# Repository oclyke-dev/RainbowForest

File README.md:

# Rainbow Forest

Rainbow Forest is an interactive experience to compose short songs on a larger-than-life musical staff. Designed for the Museum of Boulder's 2020 Plazeum 2.0 exhibit this installation engages creativity and interaction through the combination of sounds and sights.

## Firmware

There are several microcontrollers working in concert (pun intended) to make the Rainbow Forest function. They are:

- **conductor** : the main processor conducting audio operations and the overall system operation
- **network hub** : the network hub handles communication between the column controllers and the conductor 
- **column controllers** : each column of notes on the staff is managed by an individual controller

The programs that run on each of these devices can be found in ```firmware/main```

Components that are common between programs can be found in ```firmware/components```. These components are expected to be symbolically linked into the main program directories. Arduino requires additional source code to be placed within a ```src``` directory. From the repository root directory one may run the link scripts to quickly make symbolic links from every component to every main program. 

- **linux**: ```./scripts/link.sh```
- **windows**: ```scripts\link.bat```

You may also create the symbolic links manually (Linux / Windows examples follow).

- **linux**: ```ln -s firmware/components/${component} firmware/main/${program}/src/components```
- **windows**: ```mklink /J firmware\main\%program%\src\components\%component% firmware\components\%component%```

Partial / experimental programs may be contained in ```firmware/prototyping``` for reference

## Hardware

The hardware directory contains the Eagle design files and Gerber manufacturing files for the original Rainbow Forest installation.

## Web

The Rainbow Forest installation connects to the world wide web, allowing users to check in on its status from anywhere.

In the museum a single-board computer running Chromium is used as a dedicated user interface.

```
./Chromium.app/Contents/MacOS/Chromium --app=https://oclyke.dev/rainbow-forest
```

## raspberry pi
the rainbow forest uses a local raspberry pi microcomputer to provide a user interface for museum visitors. this is acheived by using Chromium in kiosk mode. the raspberry pi also translates ```ws://``` messages into ```wss://``` messages for transfer to the main server (since the esp32s were unhappy running ```wss://```) 

[headless raspberry pi configuration](https://desertbot.io/blog/headless-raspberry-pi-3-bplus-ssh-wifi-setup)
[configuring rapberry pi for kiosk mode](https://die-antwort.eu/techblog/2017-12-setup-raspberry-pi-for-kiosk-mode/)
[using systemd on the pi](https://www.raspberrypi.org/documentation/linux/usage/systemd.md)
[using node and pm2 to daemonize applications](https://dev.to/bogdaaamn/run-your-nodejs-application-on-a-headless-raspberry-pi-4jnn)
[distributions of node for raspberry pi](https://github.com/nodesource/distributions)

## License

This project is subject to the license listed in file ```LICENSE.md```

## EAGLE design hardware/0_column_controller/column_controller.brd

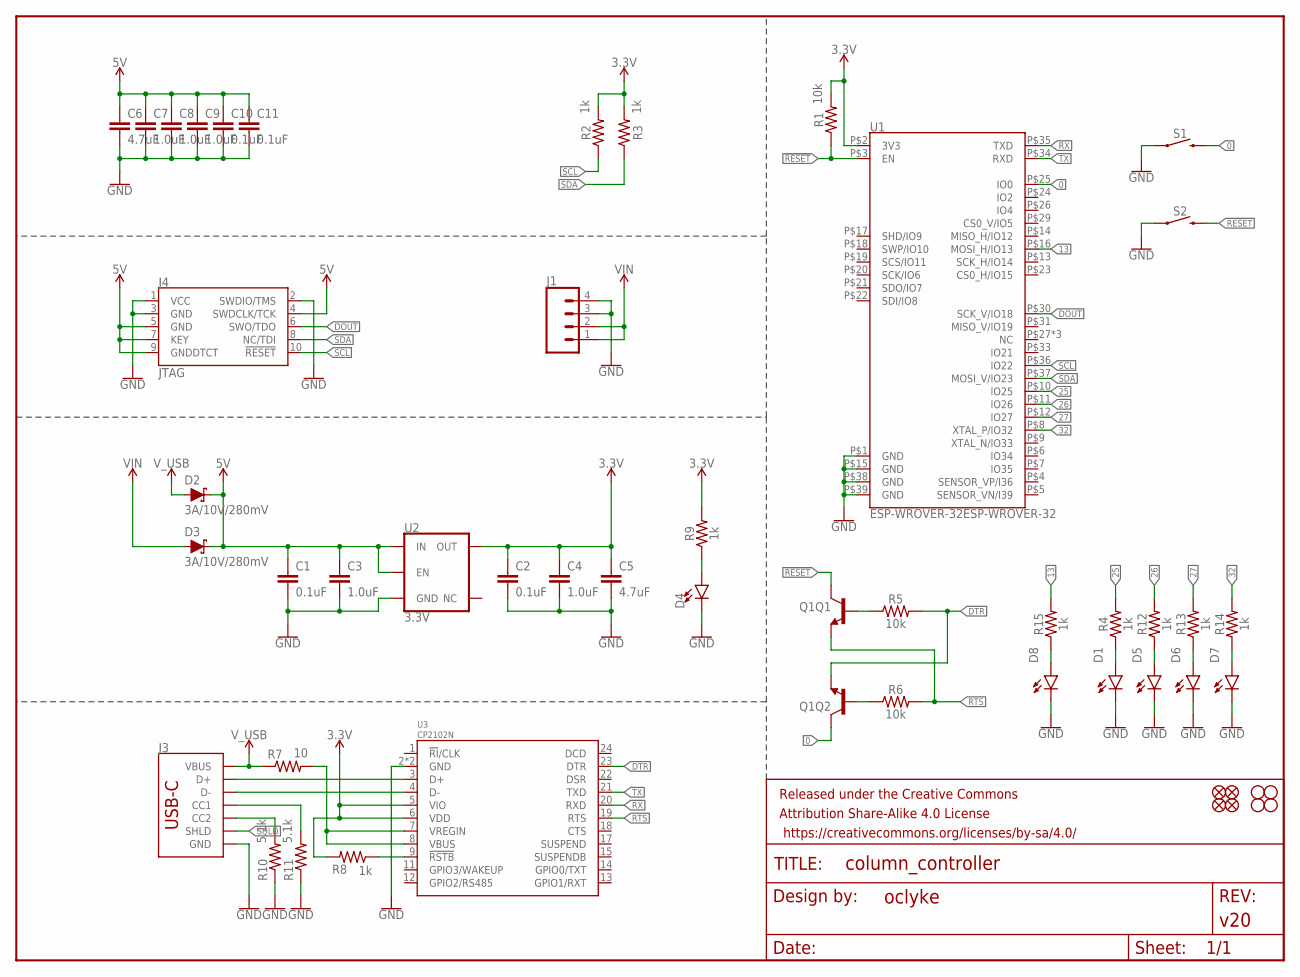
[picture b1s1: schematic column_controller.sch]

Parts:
C1, C2, C10, C11: 0.1uF; 0603
C3, C4, C7, C8, C9: 1.0uF; 0603
C5, C6: 4.7uF; 0603
D1, D5, D6, D7, D8: LED-BLUE0603; LED-0603
D2, D3: 3A/10V/280mV; SOD-323
D4: LED-RED0603; LED-0603
FD1, FD2, FD3, FD4: FIDUCIAL1X2; FIDUCIAL-1X2
FRAME1: FRAME-LETTER; CREATIVE_COMMONS
H1, H2, H3, H4: STAND-OFF#8; STAND-OFF-#8
J1: CONN_04SCREW; SCREWTERMINAL-3.5MM-4
J3: USB_C_2-LAYER; USB-C-16P
J4: JTAG; 2X5-SMD-1.27MM
Q1: TRANS_NPN_DUAL-MBT3904DW1T1; SC70-6
R1, R5, R6: 10k; 0603
R2, R3, R4, R8, R9, R12, R13, R14, R15: 1k; 0603
R7: 10; 0603
R10, R11: 5.1k; 0603
S1, S2: MOMENTARY-SWITCH-SPST-SMD-4.6X2.8MM; TACTILE_SWITCH_SMD_4.6X2.8MM
U1: ESP-WROVER-32ESP-WROVER-32; ESP-WROVER-32
U2: 3.3V; SOT23-5
U3: CP2102N; QFN24

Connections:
0: Q1.6 (C), S1.3 (2), S1.4 (2), U1.P$25 (IO0)
3.3V: C2.1, C4.1, C5.1, R1.2, R2.2, R3.2, R8.2, R9.2, U1.P$2 (3V3), U2.5 (OUT), U3.5 (VIO), U3.6 (VDD)
5V: C1.1, C3.1, C6.1, C7.1, C8.1, C9.1, C10.1, C11.1, D2.C, D3.C, J4.4 (SWDCLK/TCK), J4.5 (GND), J4.7 (KEY), J4.9 (GNDDTCT), U2.1 (IN), U2.3 (EN)
13: R15.2, U1.P$16 (MOSI_H/IO13)
25: R4.2, U1.P$10 (IO25)
26: R12.2, U1.P$11 (IO26)
27: R13.2, U1.P$12 (IO27)
32: R14.2, U1.P$8 (XTAL_P/IO32)
!RESET: Q1.3 (C), R1.1, S2.3 (2), S2.4 (2), U1.P$3 (EN)
DOUT: J4.6 (SWO/TDO), U1.P$30 (SCK_V/IO18)
DTR: Q1.1 (E), R5.2, U3.23 (DTR)
GND: C1.2, C2.2, C3.2, C4.2, C5.2, C6.2, C7.2, C8.2, C9.2, C10.2, C11.2, D1.C, D4.C, D5.C, D6.C, D7.C, D8.C, J1.3, J1.4, J3.GND, J3.GND2 (GND), J4.1 (VCC), J4.2 (SWDIO/TMS), J4.3 (GND), R10.1, R11.1, S1.1, S1.2 (1), S2.1, S2.2 (1), U1.P$1 (GND), U1.P$15 (GND), U1.P$38 (GND), U1.P$39 (GND), U2.2 (GND), U3.2 (GND), U3.PAD (GND)
unnamed: J3.A7 (D-), J3.B7 (D-), U3.4 (D-)
unnamed: J3.A6 (D+), J3.B6 (D+), U3.3 (D+)
unnamed: Q1.2 (B), R6.1
unnamed: D1.A, R4.1
unnamed: Q1.5 (B), R5.1
unnamed: R7.2, U3.7 (VREGIN), U3.8 (VBUS)
unnamed: R8.1, U3.9 (!RSTB)
unnamed: D4.A, R9.1
unnamed: D5.A, R12.1
unnamed: J3.A5 (CC1), R11.2
unnamed: J3.B5 (CC2), R10.2
unnamed: D6.A, R13.1
unnamed: D7.A, R14.1
unnamed: D8.A, R15.1
RTS: Q1.4 (E), R6.2, U3.19 (RTS)
RX: U1.P$35 (TXD), U3.20 (RXD)
SCL: J4.10 (!RESET), R2.1, U1.P$36 (IO22)
SDA: J4.8 (NC/TDI), R3.1, U1.P$37 (MOSI_V/IO23)
SHLD: J3.SHLD1 (SHLD), J3.SHLD2 (SHLD), J3.SHLD3 (SHLD), J3.SHLD4 (SHLD), J3.SHLD5 (SHLD), J3.SHLD6 (SHLD), J3.SHLD7 (SHLD), J3.SHLD8 (SHLD)
TX: U1.P$34 (RXD), U3.21 (TXD)
VIN: D3.A, J1.1, J1.2
V_USB: D2.A, J3.VBUS1 (VBUS), J3.VBUS2 (VBUS), R7.1

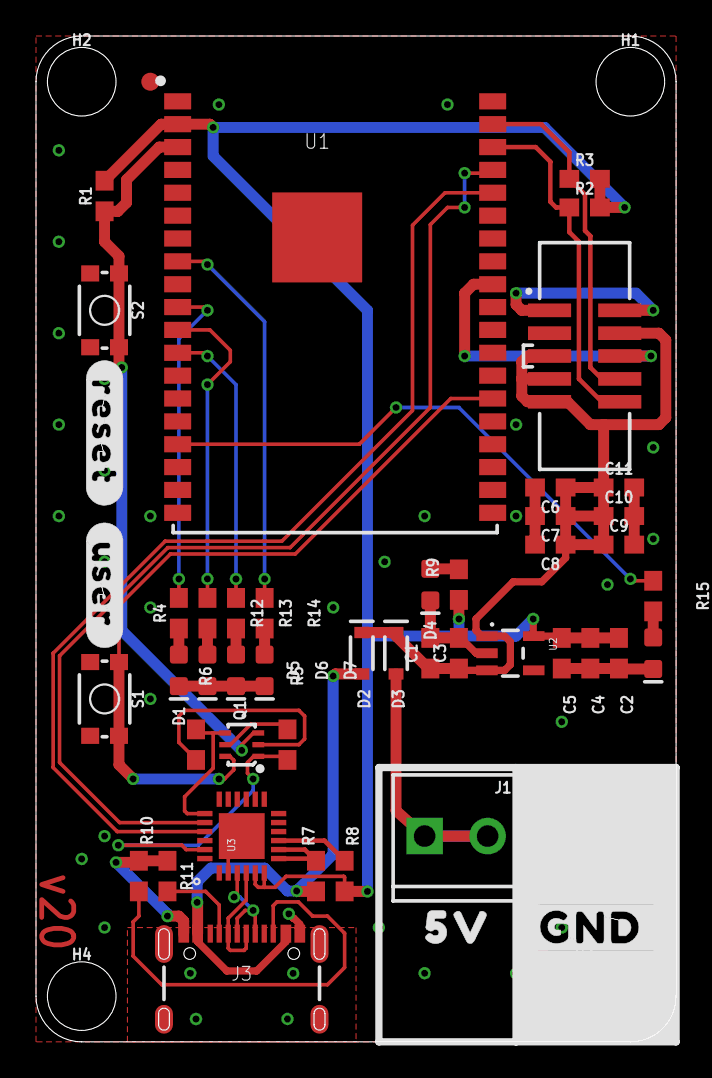
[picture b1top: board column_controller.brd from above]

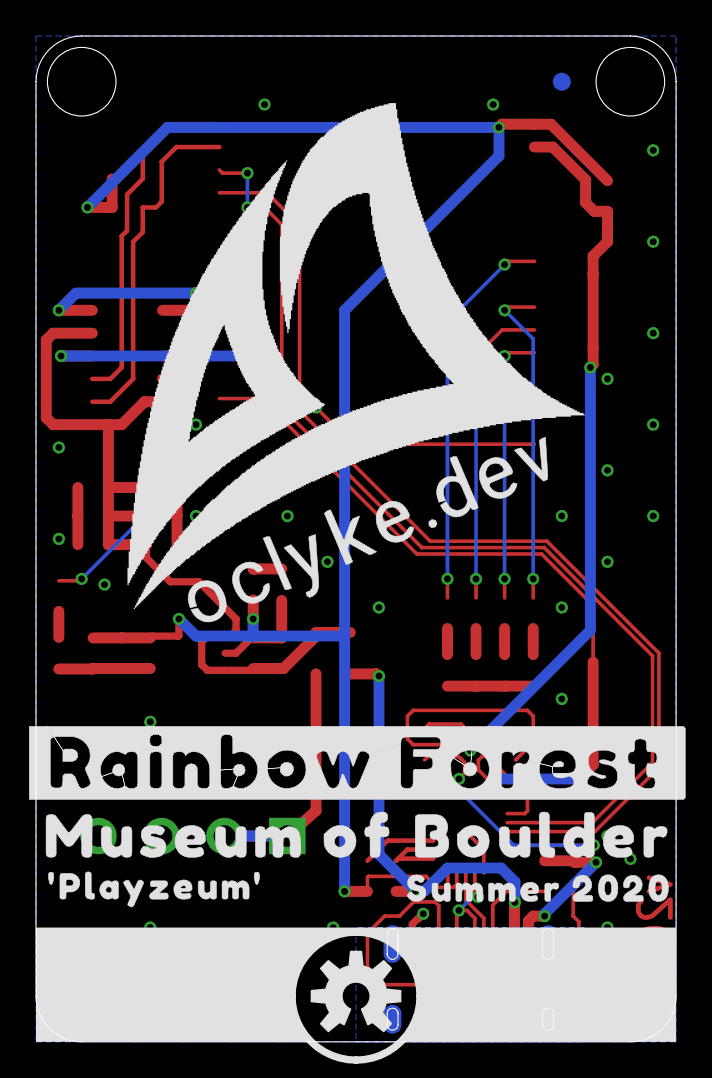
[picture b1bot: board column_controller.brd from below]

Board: 2 copper layers, 35.5 x 55.9 mm, 63 parts (9 on the bottom side), 34 nets.

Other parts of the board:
U$1: 5V2
U$2: #GND#6
U$4: #USER#2
U$5: #RESET#3
U$6: OCL_L#PNG
U$7: MUSEUM_OF_BOULDER9
U$8: OCLYKE#DEV7
U$9: #RAINBOW_FOREST#8
U$10: SUMMER_202010
U$11: #PLAYZEUM#10
U$12: OSHW-LOGO-M

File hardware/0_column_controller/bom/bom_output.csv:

Qty, PROD_ID, Names, Value, Package
4, CAP-00810, C1; C2; C10; C11, 0.1uF, 0603
5, CAP-13930, C3; C4; C7; C8; C9, 1.0uF, 0603
2, CAP-14106, C5; C6, 4.7uF, 0603
5, DIO-08575, D1; D5; D6; D7; D8, , LED-0603
2, DIO-14072, D2; D3, 3A/10V/280mV, SOD-323
1, DIO-00819, D4, , LED-0603
1, CONN-14485, J1, , SCREWTERMINAL-3.5MM-4
1, CONN-14122, J3, , USB-C-16P
1, CONN-14503, J4, JTAG, 2X5-SMD-1.27MM
1, TRANS-13337, Q1, , SC70-6
3, RES-00824, R1; R5; R6, 10k, 0603
9, RES-07856, R2; R3; R4; R8; R9; R12; R13; R14; R15, 1k, 0603
1, RES-12581, R7, 10, 0603
2, RES-12083, R10; R11, 5.1k, 0603
2, SWCH-13065, S1; S2, , TACTILE_SWITCH_SMD_4.6X2.8MM
1, , U1, ESP-WROVER-32ESP-WROVER-32, ESP-WROVER-32
1, VREG-12457, U2, 3.3V, SOT23-5
1, IC-14020, U3, CP2102N, QFN24

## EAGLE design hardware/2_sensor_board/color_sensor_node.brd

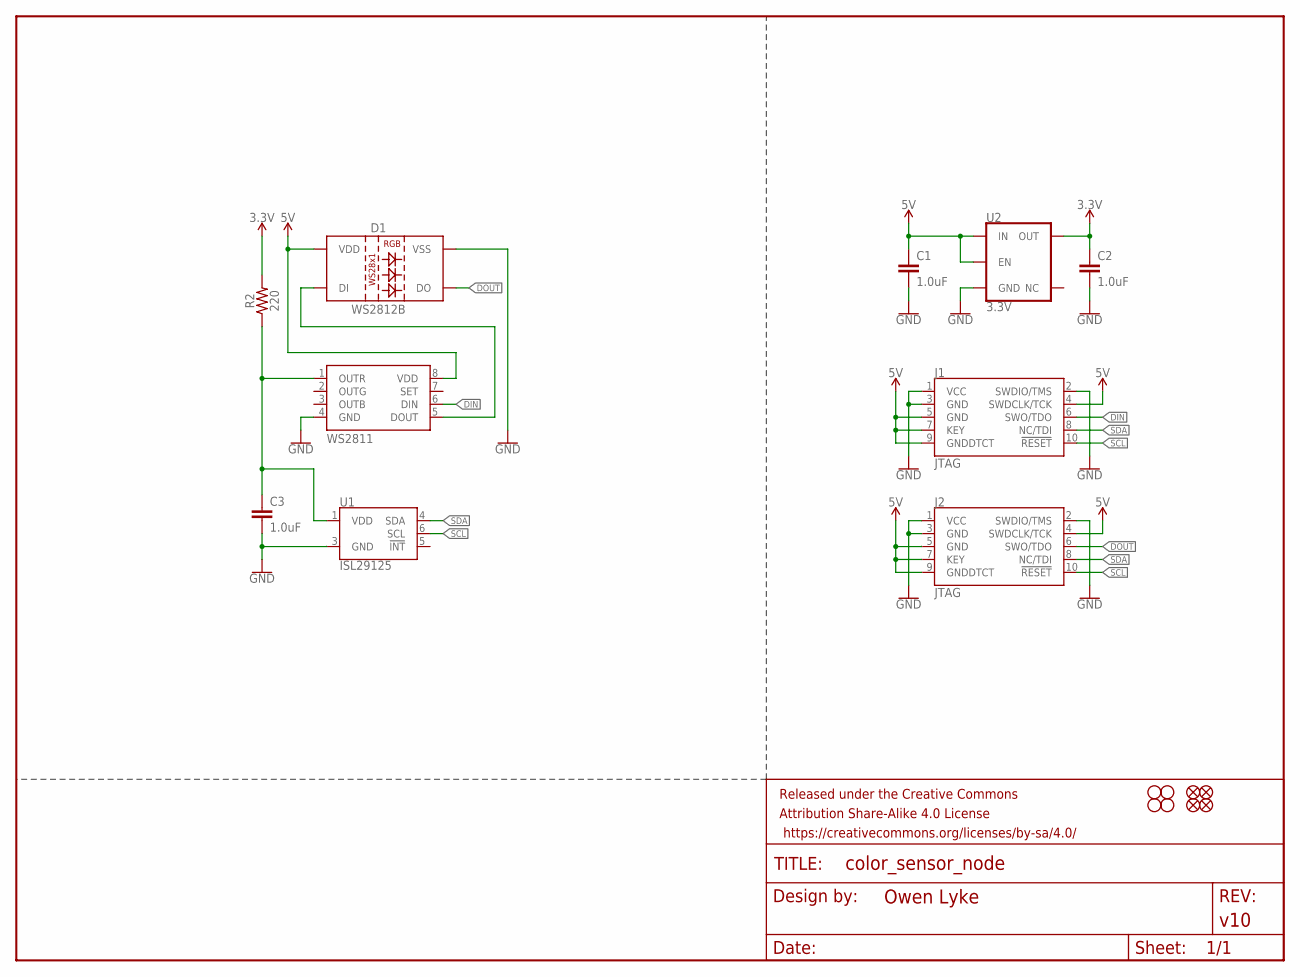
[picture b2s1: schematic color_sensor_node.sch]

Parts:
C1, C2, C3: 1.0uF; 0603
D1: WS2812B; WS2812-2020
FD1, FD2, FD3, FD4: FIDUCIAL1X2; FIDUCIAL-1X2
FRAME1: FRAME-LETTER; CREATIVE_COMMONS
H1, H2, H3, H4: STAND-OFF#8; STAND-OFF-#8
J1, J2: JTAG; 2X5-SMD-1.27MM
R2: 220; 0603
U1: ISL29125; ODFN-6
U2: 3.3V; SOT23-5
U3: WS2811; SOIC-8

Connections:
3.3V: C2.1, R2.2, U2.5 (OUT)
5V: C1.1, D1.4 (VDD), J1.4 (SWDCLK/TCK), J1.5 (GND), J1.7 (KEY), J1.9 (GNDDTCT), J2.4 (SWDCLK/TCK), J2.5 (GND), J2.7 (KEY), J2.9 (GNDDTCT), U2.1 (IN), U2.3 (EN), U3.8 (VDD)
DIN: J1.6 (SWO/TDO), U3.6 (DIN)
DOUT: D1.1 (DO), J2.6 (SWO/TDO)
GND: C1.2, C2.2, C3.2, D1.2 (VSS), J1.1 (VCC), J1.2 (SWDIO/TMS), J1.3 (GND), J2.1 (VCC), J2.2 (SWDIO/TMS), J2.3 (GND), U1.3 (GND), U2.2 (GND), U3.4 (GND)
unnamed: C3.1, R2.1, U1.1 (VDD), U3.1 (OUTR)
unnamed: D1.3 (DI), U3.5 (DOUT)
SCL: J1.10 (!RESET), J2.10 (!RESET), U1.6 (SCL)
SDA: J1.8 (NC/TDI), J2.8 (NC/TDI), U1.4 (SDA)

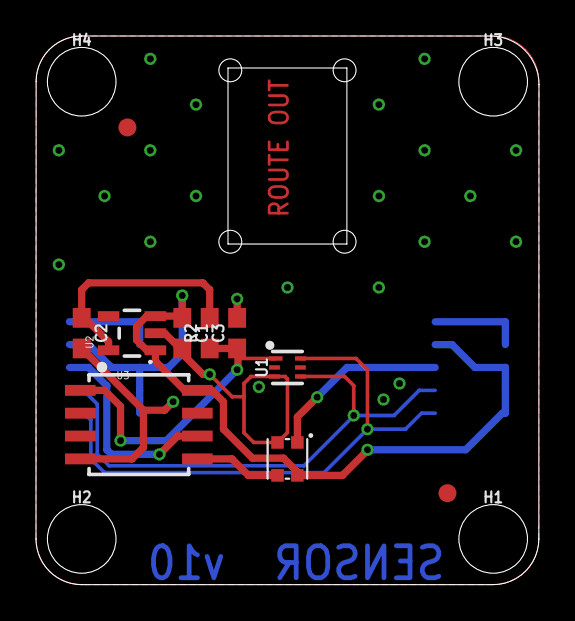
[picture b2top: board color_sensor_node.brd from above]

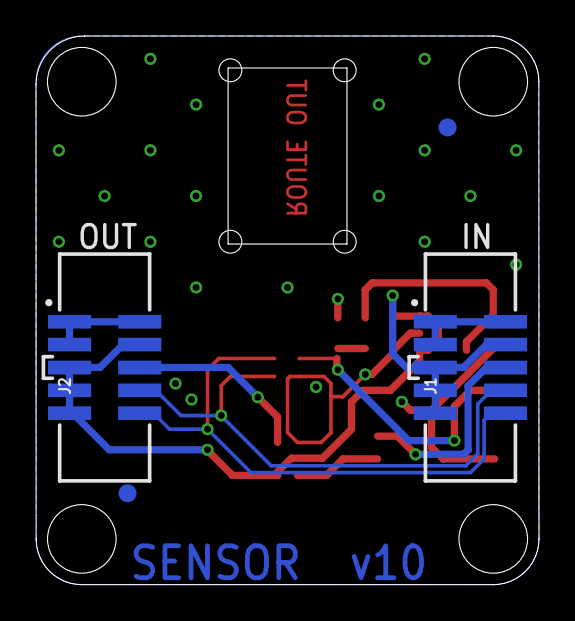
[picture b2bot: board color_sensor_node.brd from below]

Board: 2 copper layers, 27.9 x 30.5 mm, 19 parts (4 on the bottom side), 9 nets.

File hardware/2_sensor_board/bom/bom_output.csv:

Qty, PROD_ID, Names, Value, Package
3, CAP-00868, C1; C2; C3, 1.0uF, 0603
1, , D1, WS2812B, WS2812-2020
2, CONN-14503, J1; J2, JTAG, 2X5-SMD-1.27MM
1, RES-07861, R2, 220, 0603
1, IC-12055, U1, ISL29125, ODFN-6
1, VREG-12457, U2, 3.3V, SOT23-5
1, , U3, WS2811, SOIC-8

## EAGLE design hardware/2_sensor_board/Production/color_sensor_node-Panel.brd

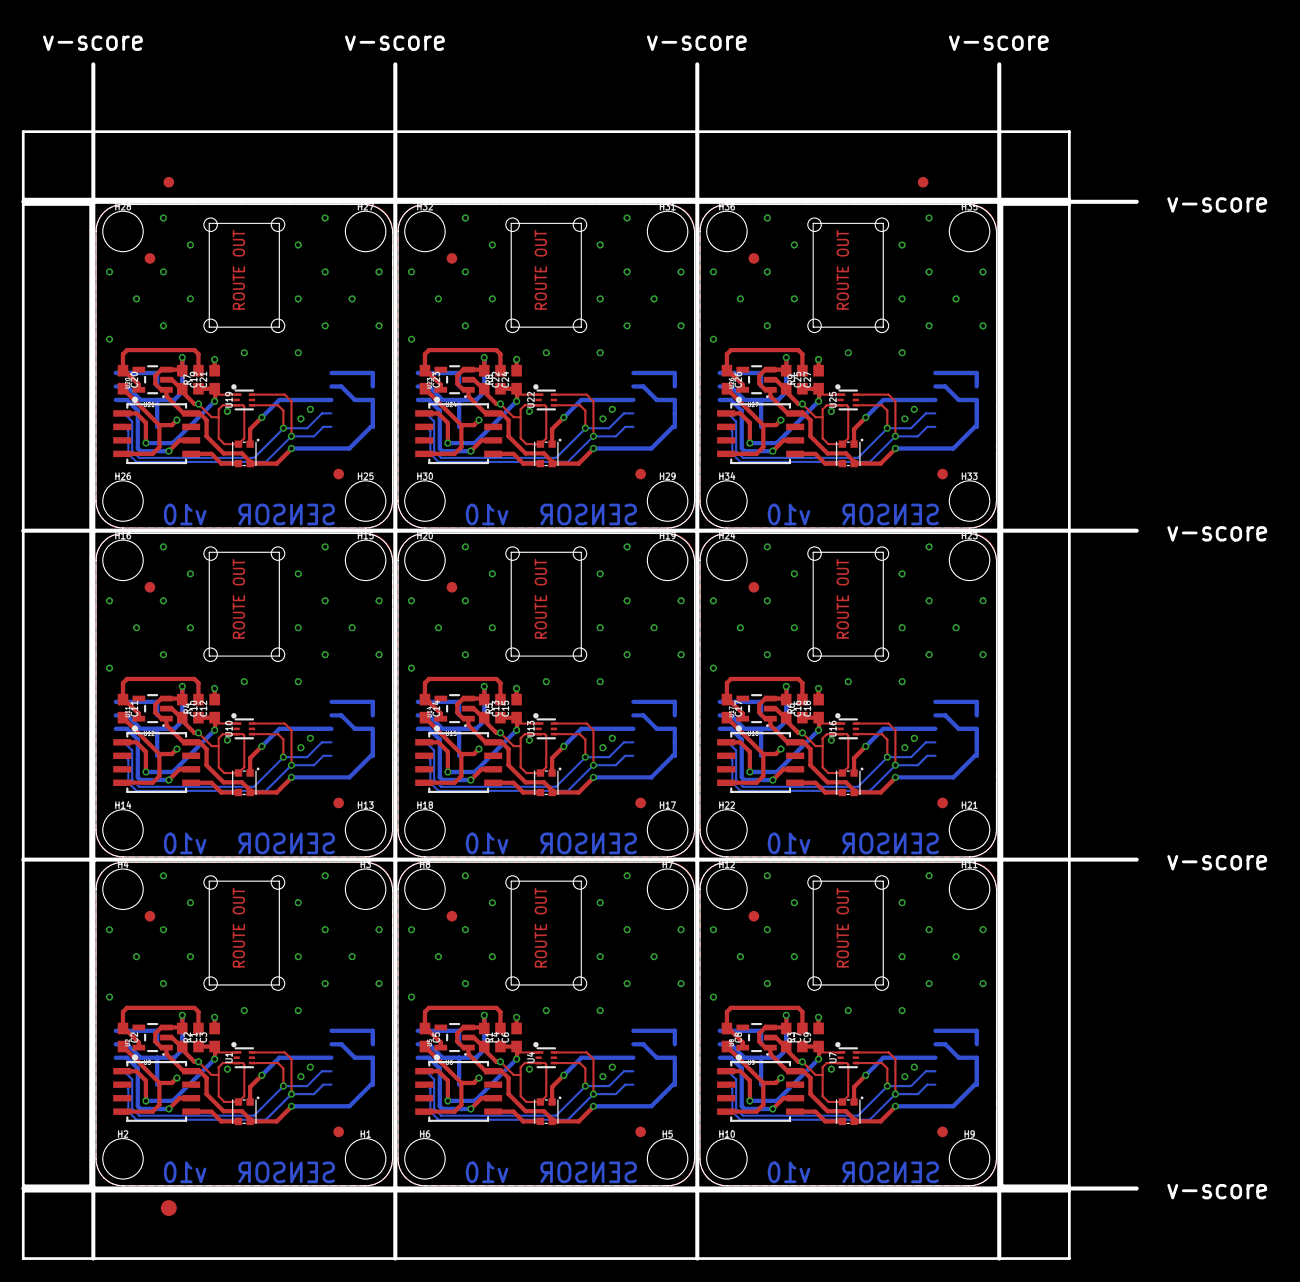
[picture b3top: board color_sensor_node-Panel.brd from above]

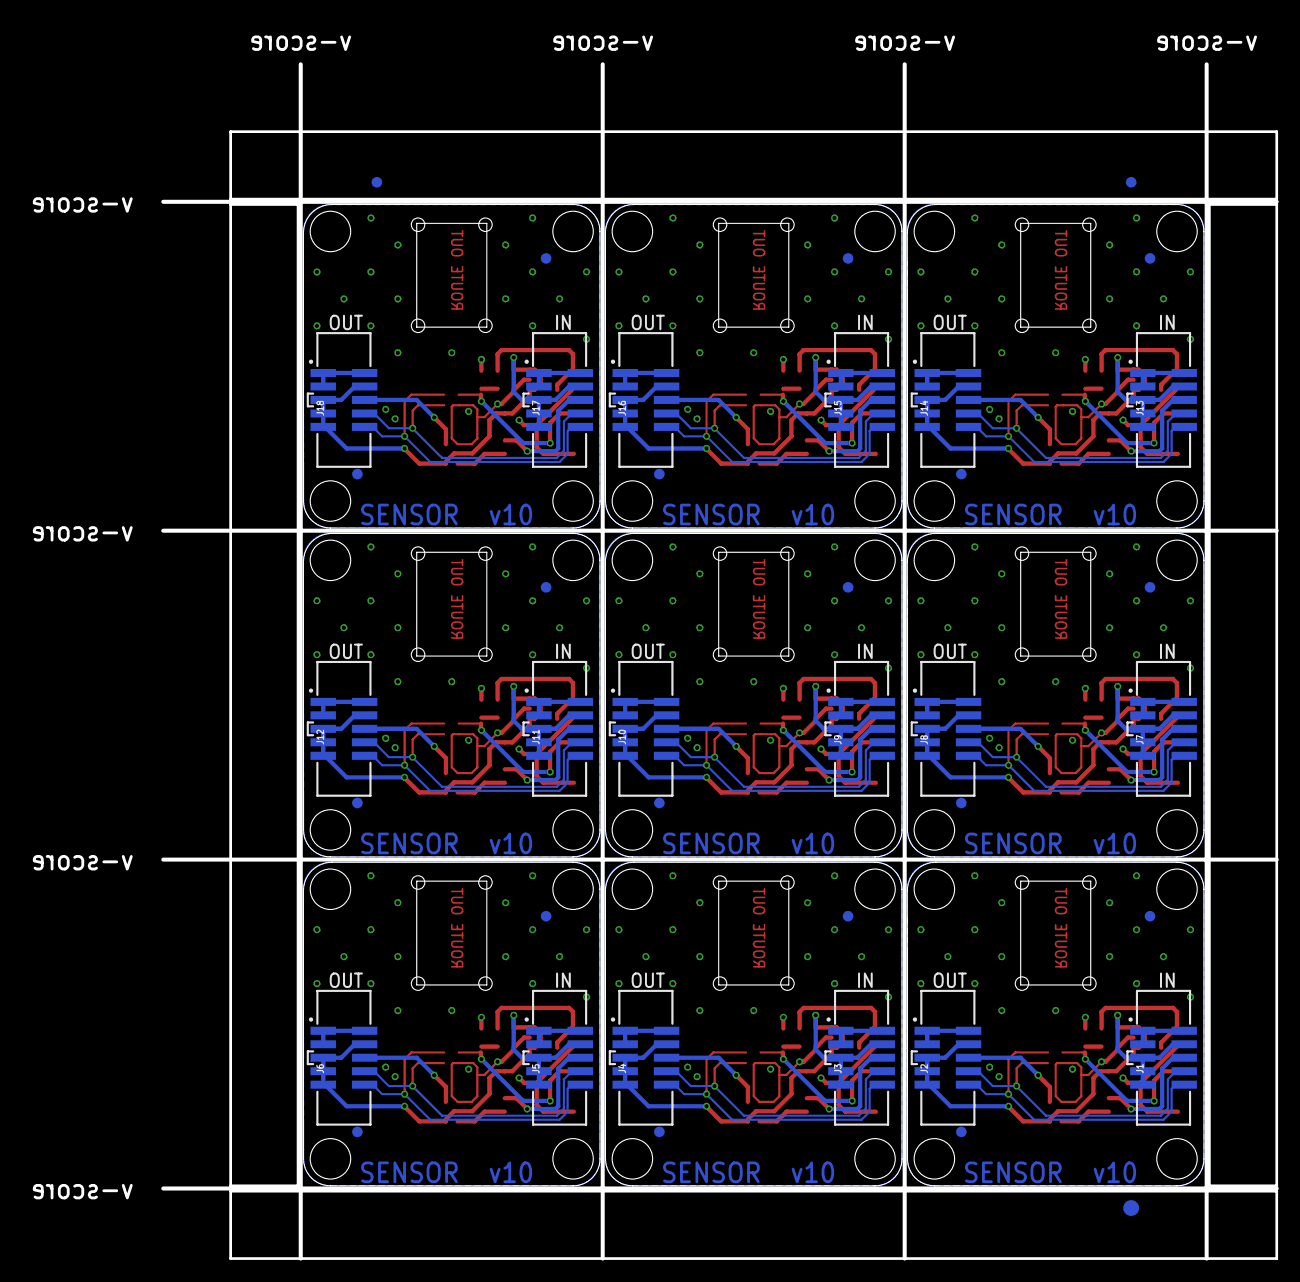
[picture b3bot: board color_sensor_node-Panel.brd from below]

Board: 2 copper layers, 118.1 x 116.4 mm, 168 parts (39 on the bottom side), 81 nets.

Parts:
C1, C2, C3, C4, C5, C6, C7, C8, C9, C10, C11, C12, C13, C14, C15, C16, C17, C18, C19, C20, C21, C22, C23, C24, C25, C26, C27: 1.0uF; 0603
D1, D2, D3, D4, D5, D6, D7, D8, D9: WS2812B; WS2812-2020
E$1, E$2, E$3, E$4: FIDUCIAL-1X2
E$5, E$6: FIDUCIAL-1.5X3
FD1, FD2, FD3, FD4, FD5, FD6, FD7, FD8, FD9, FD10, FD11, FD12, FD13, FD14, FD15, FD16, FD17, FD18, FD19, FD20, FD21, FD22, FD23, FD24, FD25, FD26, FD27, FD28, FD29, FD30, FD31, FD32, FD33, FD34, FD35, FD36: FIDUCIAL1X2; FIDUCIAL-1X2
H1, H2, H3, H4, H5, H6, H7, H8, H9, H10, H11, H12, H13, H14, H15, H16, H17, H18, H19, H20, H21, H22, H23, H24, H25, H26, H27, H28, H29, H30, H31, H32, H33, H34, H35, H36: STAND-OFF#8; STAND-OFF-#8
J1, J2, J3, J4, J5, J6, J7, J8, J9, J10, J11, J12, J13, J14, J15, J16, J17, J18: JTAG; 2X5-SMD-1.27MM
R1, R2, R3, R4, R5, R6, R7, R8, R9: 220; 0603
U1, U4, U7, U10, U13, U16, U19, U22, U25: ISL29125; ODFN-6
U2, U5, U8, U11, U14, U17, U20, U23, U26: 3.3V; SOT23-5
U3, U6, U9, U12, U15, U18, U21, U24, U27: WS2811; SOIC-8

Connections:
3.3V: C2.1, R2.2, U2.5
3.3V1: C5.1, R1.2, U5.5
3.3V2: C8.1, R3.2, U8.5
3.3V3: C11.1, R4.2, U11.5
3.3V4: C14.1, R5.2, U14.5
3.3V5: C17.1, R6.2, U17.5
3.3V6: C20.1, R7.2, U20.5
3.3V7: C23.1, R8.2, U23.5
3.3V8: C26.1, R9.2, U26.5
5V: C1.1, D1.4, J1.4, J1.5, J1.7, J1.9, J2.4, J2.5, J2.7, J2.9, U2.1, U2.3, U3.8
5V1: C4.1, D2.4, J3.4, J3.5, J3.7, J3.9, J4.4, J4.5, J4.7, J4.9, U5.1, U5.3, U6.8
5V2: C7.1, D3.4, J5.4, J5.5, J5.7, J5.9, J6.4, J6.5, J6.7, J6.9, U8.1, U8.3, U9.8
5V3: C10.1, D4.4, J7.4, J7.5, J7.7, J7.9, J8.4, J8.5, J8.7, J8.9, U11.1, U11.3, U12.8
5V4: C13.1, D5.4, J9.4, J9.5, J9.7, J9.9, J10.4, J10.5, J10.7, J10.9, U14.1, U14.3, U15.8
5V5: C16.1, D6.4, J11.4, J11.5, J11.7, J11.9, J12.4, J12.5, J12.7, J12.9, U17.1, U17.3, U18.8
5V6: C19.1, D7.4, J13.4, J13.5, J13.7, J13.9, J14.4, J14.5, J14.7, J14.9, U20.1, U20.3, U21.8
5V7: C22.1, D8.4, J15.4, J15.5, J15.7, J15.9, J16.4, J16.5, J16.7, J16.9, U23.1, U23.3, U24.8
5V8: C25.1, D9.4, J17.4, J17.5, J17.7, J17.9, J18.4, J18.5, J18.7, J18.9, U26.1, U26.3, U27.8
DIN: J1.6, U3.6
DIN1: J3.6, U6.6
DIN2: J5.6, U9.6
DIN3: J7.6, U12.6
DIN4: J9.6, U15.6
DIN5: J11.6, U18.6
DIN6: J13.6, U21.6
DIN7: J15.6, U24.6
DIN8: J17.6, U27.6
DOUT: D1.1, J2.6
DOUT1: D2.1, J4.6
DOUT2: D3.1, J6.6
DOUT3: D4.1, J8.6
DOUT4: D5.1, J10.6
DOUT5: D6.1, J12.6
DOUT6: D7.1, J14.6
DOUT7: D8.1, J16.6
DOUT8: D9.1, J18.6
GND: C1.2, C2.2, C3.2, D1.2, J1.1, J1.2, J1.3, J2.1, J2.2, J2.3, U1.3, U2.2, U3.4
GND1: C4.2, C5.2, C6.2, D2.2, J3.1, J3.2, J3.3, J4.1, J4.2, J4.3, U4.3, U5.2, U6.4
GND2: C7.2, C8.2, C9.2, D3.2, J5.1, J5.2, J5.3, J6.1, J6.2, J6.3, U7.3, U8.2, U9.4
GND3: C10.2, C11.2, C12.2, D4.2, J7.1, J7.2, J7.3, J8.1, J8.2, J8.3, U10.3, U11.2, U12.4
GND4: C13.2, C14.2, C15.2, D5.2, J9.1, J9.2, J9.3, J10.1, J10.2, J10.3, U13.3, U14.2, U15.4
GND5: C16.2, C17.2, C18.2, D6.2, J11.1, J11.2, J11.3, J12.1, J12.2, J12.3, U16.3, U17.2, U18.4
GND6: C19.2, C20.2, C21.2, D7.2, J13.1, J13.2, J13.3, J14.1, J14.2, J14.3, U19.3, U20.2, U21.4
GND7: C22.2, C23.2, C24.2, D8.2, J15.1, J15.2, J15.3, J16.1, J16.2, J16.3, U22.3, U23.2, U24.4
GND8: C25.2, C26.2, C27.2, D9.2, J17.1, J17.2, J17.3, J18.1, J18.2, J18.3, U25.3, U26.2, U27.4
unnamed: D2.3, U6.5
unnamed: C3.1, R2.1, U1.1, U3.1
unnamed: C6.1, R1.1, U4.1, U6.1
unnamed: D1.3, U3.5
unnamed: D3.3, U9.5
unnamed: C9.1, R3.1, U7.1, U9.1
unnamed: D4.3, U12.5
unnamed: C12.1, R4.1, U10.1, U12.1
unnamed: D5.3, U15.5
unnamed: C15.1, R5.1, U13.1, U15.1
unnamed: D6.3, U18.5
unnamed: C18.1, R6.1, U16.1, U18.1
unnamed: D7.3, U21.5
unnamed: C21.1, R7.1, U19.1, U21.1
unnamed: D8.3, U24.5
unnamed: C24.1, R8.1, U22.1, U24.1
unnamed: D9.3, U27.5
unnamed: C27.1, R9.1, U25.1, U27.1
SCL: J1.10, J2.10, U1.6
SCL1: J3.10, J4.10, U4.6
SCL2: J5.10, J6.10, U7.6
SCL3: J7.10, J8.10, U10.6
SCL4: J9.10, J10.10, U13.6
SCL5: J11.10, J12.10, U16.6
SCL6: J13.10, J14.10, U19.6
SCL7: J15.10, J16.10, U22.6
SCL8: J17.10, J18.10, U25.6
SDA: J1.8, J2.8, U1.4
SDA1: J3.8, J4.8, U4.4
SDA2: J5.8, J6.8, U7.4
SDA3: J7.8, J8.8, U10.4
SDA4: J9.8, J10.8, U13.4
SDA5: J11.8, J12.8, U16.4
SDA6: J13.8, J14.8, U19.4
SDA7: J15.8, J16.8, U22.4
SDA8: J17.8, J18.8, U25.4

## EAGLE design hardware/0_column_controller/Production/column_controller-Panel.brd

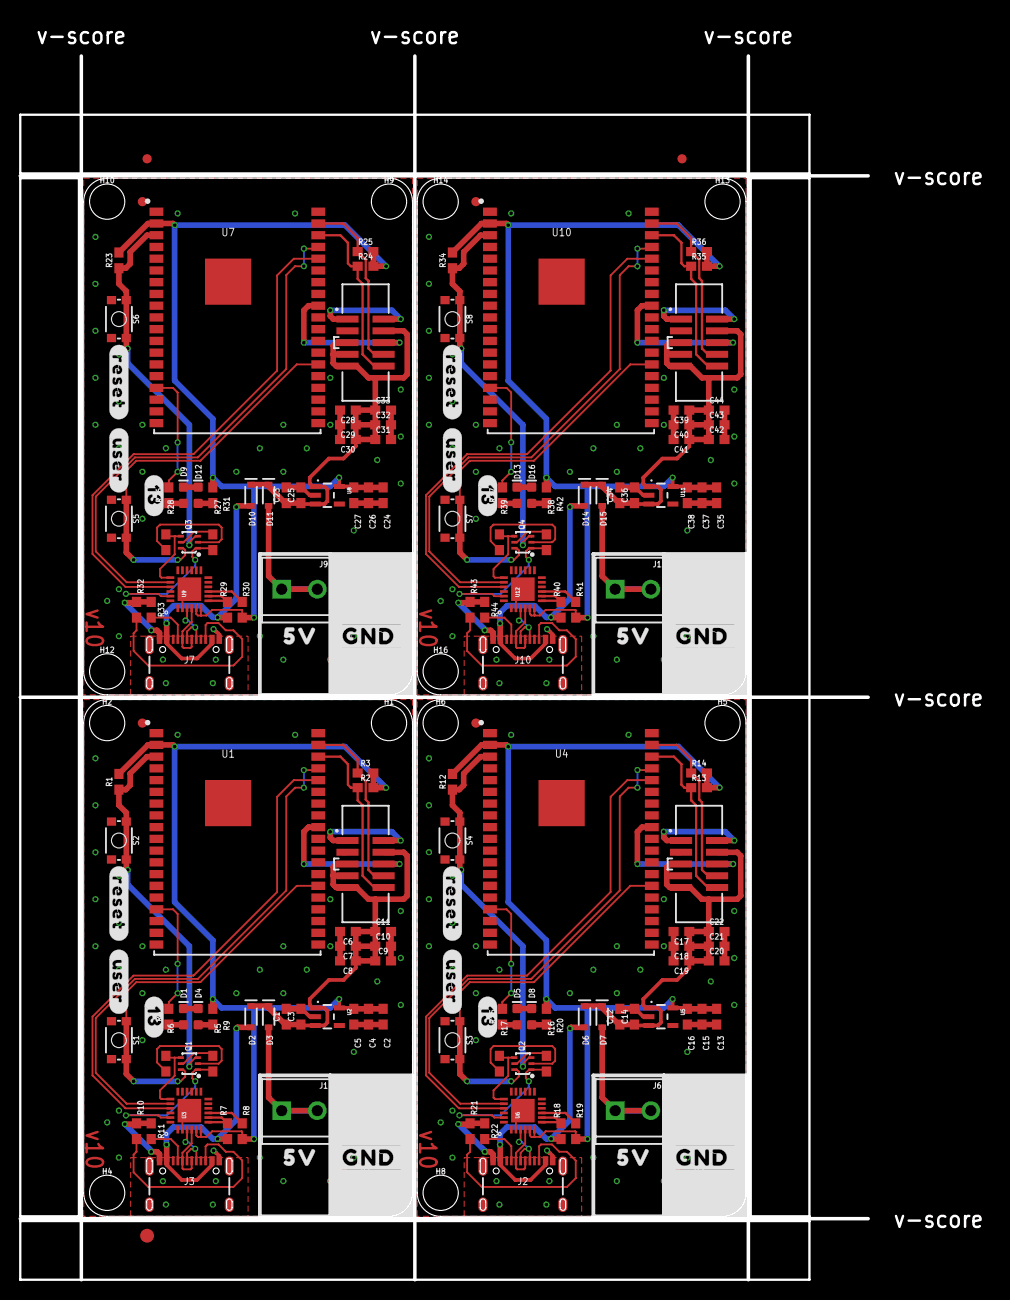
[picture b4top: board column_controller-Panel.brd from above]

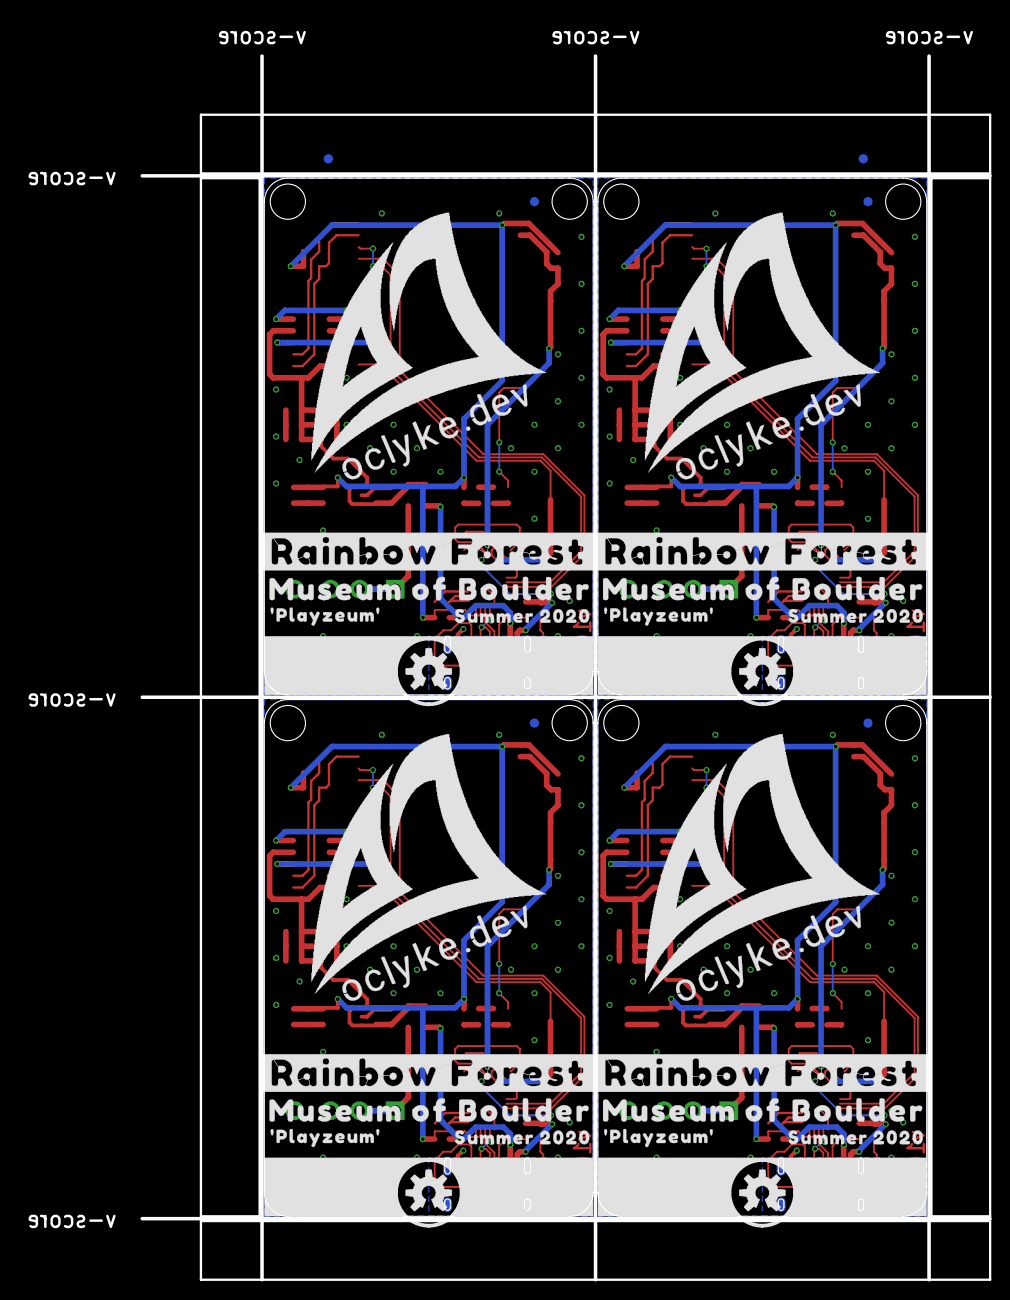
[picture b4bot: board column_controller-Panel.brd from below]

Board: 2 copper layers, 104.9 x 136.2 mm, 225 parts (38 on the bottom side), 104 nets.

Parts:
C1, C2, C10, C11, C12, C13, C21, C22, C23, C24, C32, C33, C34, C35, C43, C44: 0.1uF; 0603
C3, C4, C7, C8, C9, C14, C15, C18, C19, C20, C25, C26, C29, C30, C31, C36, C37, C40, C41, C42: 1.0uF; 0603
C5, C6, C16, C17, C27, C28, C38, C39: 4.7uF; 0603
D1, D5, D9, D13: 13; LED-0603
D2, D3, D6, D7, D10, D11, D14, D15: 3A/10V/280mV; SOD-323
D4, D8, D12, D16: POWER; LED-0603
E$1, E$2, E$3, E$4: FIDUCIAL-1X2
E$5: FIDUCIAL-1.5X3
FD1, FD2, FD3, FD4, FD5, FD6, FD7, FD8, FD9, FD10, FD11, FD12, FD13, FD14, FD15, FD16: FIDUCIAL1X2; FIDUCIAL-1X2
H1, H2, H3, H4, H5, H6, H7, H8, H9, H10, H11, H12, H13, H14, H15, H16: STAND-OFF#8; STAND-OFF-#8
J1, J6, J9, J12: SCREWTERMINAL-3.5MM-4_LOCK
J2, J3, J7, J10: USB-C-16P
J4, J5, J8, J11: JTAG; 2X5-SMD-1.27MM
Q1, Q2, Q3, Q4: SC70-6
R1, R5, R6, R12, R16, R17, R23, R27, R28, R34, R38, R39: 10k; 0603
R2, R3, R8, R13, R14, R19, R24, R25, R30, R35, R36, R41: 1k; 0603
R4, R9, R15, R20, R26, R31, R37, R42: 330; 0603
R7, R18, R29, R40: 10; 0603
R10, R11, R21, R22, R32, R33, R43, R44: 5.1k; 0603
S1, S3, S5, S7: Button 0; TACTILE_SWITCH_SMD_4.6X2.8MM
S2, S4, S6, S8: !RESET; TACTILE_SWITCH_SMD_4.6X2.8MM
U1, U4, U7, U10: ESP-WROVER-32ESP-WROVER-32; ESP-WROVER-32
U2, U5, U8, U11: 3.3V; SOT23-5
U3, U6, U9, U12: CP2102N; QFN24
U$1, U$13, U$25, U$37: 5V2
U$2, U$14, U$26, U$38: #GND#6
U$3, U$15, U$27, U$39: #13#0
U$4, U$16, U$28, U$40: #USER#2
U$5, U$17, U$29, U$41: #RESET#3
U$6, U$18, U$30, U$42: OCL_L#PNG
U$7, U$20, U$32, U$44: MUSEUM_OF_BOULDER9
U$8, U$19, U$31, U$43: OCLYKE#DEV7
U$9, U$21, U$33, U$45: #RAINBOW_FOREST#8
U$10, U$22, U$34, U$46: SUMMER_202010
U$11, U$23, U$35, U$47: #PLAYZEUM#10
U$12, U$24, U$36, U$48: OSHW-LOGO-M

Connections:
0: Q1.6, S1.3, S1.4, U1.P$25
1: Q2.6, S3.3, S3.4, U4.P$25
2: R15.2, U4.P$16
3: Q3.6, S5.3, S5.4, U7.P$25
3.3V: C2.1, C4.1, C5.1, R1.2, R2.2, R3.2, R8.2, R9.2, U1.P$2, U2.5, U3.5, U3.6
3.3V1: C13.1, C15.1, C16.1, R12.2, R13.2, R14.2, R19.2, R20.2, U4.P$2, U5.5, U6.5, U6.6
3.3V2: C24.1, C26.1, C27.1, R23.2, R24.2, R25.2, R30.2, R31.2, U7.P$2, U8.5, U9.5, U9.6
3.3V3: C35.1, C37.1, C38.1, R34.2, R35.2, R36.2, R41.2, R42.2, U10.P$2, U11.5, U12.5, U12.6
4: R26.2, U7.P$16
5: Q4.6, S7.3, S7.4, U10.P$25
5V: C1.1, C3.1, C6.1, C7.1, C8.1, C9.1, C10.1, C11.1, D2.C, D3.C, J4.4, J4.5, J4.7, J4.9, U2.1, U2.3
5V1: C12.1, C14.1, C17.1, C18.1, C19.1, C20.1, C21.1, C22.1, D6.C, D7.C, J5.4, J5.5, J5.7, J5.9, U5.1, U5.3
5V2: C23.1, C25.1, C28.1, C29.1, C30.1, C31.1, C32.1, C33.1, D10.C, D11.C, J8.4, J8.5, J8.7, J8.9, U8.1, U8.3
5V3: C34.1, C36.1, C39.1, C40.1, C41.1, C42.1, C43.1, C44.1, D14.C, D15.C, J11.4, J11.5, J11.7, J11.9, U11.1, U11.3
6: R37.2, U10.P$16
13: R4.2, U1.P$16
!RESET: Q1.3, R1.1, S2.3, S2.4, U1.P$3
!RESET1: Q2.3, R12.1, S4.3, S4.4, U4.P$3
!RESET2: Q3.3, R23.1, S6.3, S6.4, U7.P$3
!RESET3: Q4.3, R34.1, S8.3, S8.4, U10.P$3
DOUT: J4.6, U1.P$30
DOUT1: J5.6, U4.P$30
DOUT2: J8.6, U7.P$30
DOUT3: J11.6, U10.P$30
DTR: Q1.1, R5.2, U3.23
DTR1: Q2.1, R16.2, U6.23
DTR2: Q3.1, R27.2, U9.23
DTR3: Q4.1, R38.2, U12.23
GND: C1.2, C2.2, C3.2, C4.2, C5.2, C6.2, C7.2, C8.2, C9.2, C10.2, C11.2, D1.C, D4.C, J1.3, J1.4, J3.GND, J3.GND2, J4.1, J4.2, J4.3, R10.1, R11.1, S1.1, S1.2, S2.1, S2.2, U1.P$1, U1.P$15, U1.P$38, U1.P$39, U2.2, U3.2, U3.PAD
GND1: C12.2, C13.2, C14.2, C15.2, C16.2, C17.2, C18.2, C19.2, C20.2, C21.2, C22.2, D5.C, D8.C, J2.GND, J2.GND2, J5.1, J5.2, J5.3, J6.3, J6.4, R21.1, R22.1, S3.1, S3.2, S4.1, S4.2, U4.P$1, U4.P$15, U4.P$38, U4.P$39, U5.2, U6.2, U6.PAD
GND2: C23.2, C24.2, C25.2, C26.2, C27.2, C28.2, C29.2, C30.2, C31.2, C32.2, C33.2, D9.C, D12.C, J7.GND, J7.GND2, J8.1, J8.2, J8.3, J9.3, J9.4, R32.1, R33.1, S5.1, S5.2, S6.1, S6.2, U7.P$1, U7.P$15, U7.P$38, U7.P$39, U8.2, U9.2, U9.PAD
GND3: C34.2, C35.2, C36.2, C37.2, C38.2, C39.2, C40.2, C41.2, C42.2, C43.2, C44.2, D13.C, D16.C, J10.GND, J10.GND2, J11.1, J11.2, J11.3, J12.3, J12.4, R43.1, R44.1, S7.1, S7.2, S8.1, S8.2, U10.P$1, U10.P$15, U10.P$38, U10.P$39, U11.2, U12.2, U12.PAD
unnamed: J3.A7, J3.B7, U3.4
unnamed: J3.A6, J3.B6, U3.3
unnamed: Q1.2, R6.1
unnamed: D1.A, R4.1
unnamed: Q1.5, R5.1
unnamed: R7.2, U3.7, U3.8
unnamed: R8.1, U3.9
unnamed: D4.A, R9.1
unnamed: D5.A, R15.1
unnamed: J3.A5, R11.2
unnamed: J3.B5, R10.2
unnamed: Q2.2, R17.1
unnamed: Q2.5, R16.1
unnamed: J2.A7, J2.B7, U6.4
unnamed: J2.A6, J2.B6, U6.3
unnamed: R18.2, U6.7, U6.8
unnamed: R19.1, U6.9
unnamed: D8.A, R20.1
unnamed: J2.A5, R22.2
unnamed: J2.B5, R21.2
unnamed: D9.A, R26.1
unnamed: Q3.2, R28.1
unnamed: Q3.5, R27.1
unnamed: J7.A7, J7.B7, U9.4
unnamed: J7.A6, J7.B6, U9.3
unnamed: R29.2, U9.7, U9.8
unnamed: R30.1, U9.9
unnamed: D12.A, R31.1
unnamed: J7.A5, R33.2
unnamed: J7.B5, R32.2
unnamed: D13.A, R37.1
unnamed: Q4.2, R39.1
unnamed: Q4.5, R38.1
unnamed: J10.A7, J10.B7, U12.4
unnamed: J10.A6, J10.B6, U12.3
unnamed: R40.2, U12.7, U12.8
unnamed: R41.1, U12.9
unnamed: D16.A, R42.1
unnamed: J10.A5, R44.2
unnamed: J10.B5, R43.2
RTS: Q1.4, R6.2, U3.19
RTS1: Q2.4, R17.2, U6.19
RTS2: Q3.4, R28.2, U9.19
RTS3: Q4.4, R39.2, U12.19
RX: U1.P$35, U3.20
RX1: U4.P$35, U6.20
RX2: U7.P$35, U9.20
RX3: U10.P$35, U12.20
SCL: J4.10, R2.1, U1.P$36
SCL1: J5.10, R13.1, U4.P$36
SCL2: J8.10, R24.1, U7.P$36
SCL3: J11.10, R35.1, U10.P$36
SDA: J4.8, R3.1, U1.P$37
SDA1: J5.8, R14.1, U4.P$37
SDA2: J8.8, R25.1, U7.P$37
SDA3: J11.8, R36.1, U10.P$37
SHLD: J3.SHLD1, J3.SHLD2, J3.SHLD3, J3.SHLD4, J3.SHLD5, J3.SHLD6, J3.SHLD7, J3.SHLD8
SHLD1: J2.SHLD1, J2.SHLD2, J2.SHLD3, J2.SHLD4, J2.SHLD5, J2.SHLD6, J2.SHLD7, J2.SHLD8
SHLD2: J7.SHLD1, J7.SHLD2, J7.SHLD3, J7.SHLD4, J7.SHLD5, J7.SHLD6, J7.SHLD7, J7.SHLD8
SHLD3: J10.SHLD1, J10.SHLD2, J10.SHLD3, J10.SHLD4, J10.SHLD5, J10.SHLD6, J10.SHLD7, J10.SHLD8
TX: U1.P$34, U3.21
TX1: U4.P$34, U6.21
TX2: U7.P$34, U9.21
TX3: U10.P$34, U12.21
VIN: D3.A, J1.1, J1.2
VIN1: D7.A, J6.1, J6.2
VIN2: D11.A, J9.1, J9.2
VIN3: D15.A, J12.1, J12.2
V_USB: D2.A, J3.VBUS1, J3.VBUS2, R7.1
V_USB1: D6.A, J2.VBUS1, J2.VBUS2, R18.1
V_USB2: D10.A, J7.VBUS1, J7.VBUS2, R29.1
V_USB3: D14.A, J10.VBUS1, J10.VBUS2, R40.1

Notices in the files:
parts and their libraries:
SparkFun-Aesthetics: Licensing: Creative Commons ShareAlike 4.0 International - https://creativecommons.org/licenses/by-sa/4.0
SparkFun-Aesthetics: Released under the Creative Commons Attribution Share-Alike 4.0 License
SparkFun-Aesthetics: https://creativecommons.org/licenses/by-sa/4.0
